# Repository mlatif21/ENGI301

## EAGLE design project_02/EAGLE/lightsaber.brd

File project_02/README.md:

# Lightsaber PCB Design

This directory in the repository contains the files for Project02, creating a circuit board based on our implemented project using PocketBeagle. All files necessary for PCB manufacturing are found here.

The docs folder contains the project 02 proposal with mechanical block diagram. It also contains a PDF of the schematics and images of the top and bottom layers of the board.

The EAGLE folder contains the library (lbr), schematics (sch), and layout (brd) files for the PCB design.
The MFG sub-folder contains the manufacturing files (Gerber, Drill, and Assembly) generated from default CAM settings.

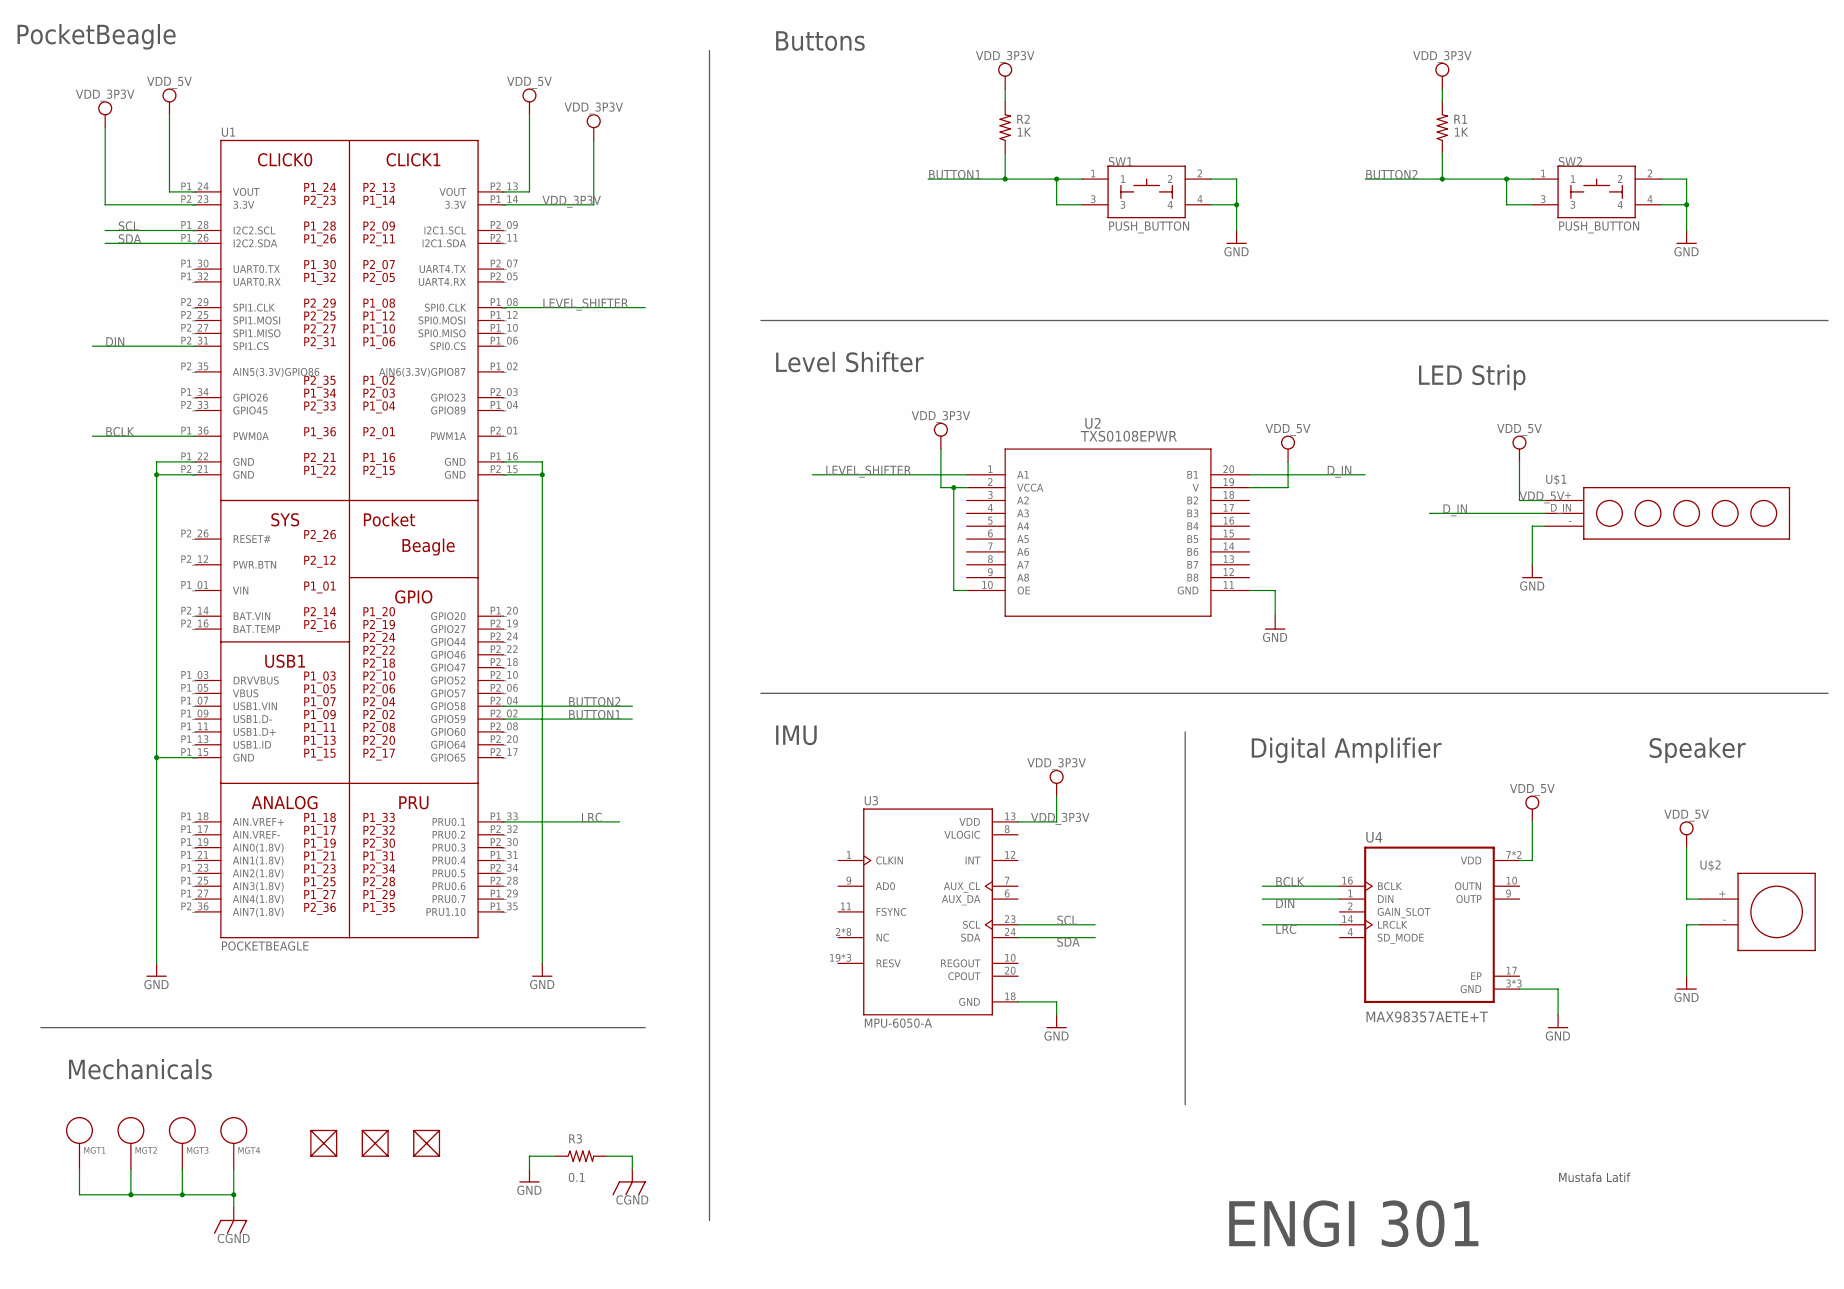
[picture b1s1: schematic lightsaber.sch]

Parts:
FUD1, FUD2, FUD3: FIDUCIAL; FIDUCIAL_40MIL
MGT1, MGT2, MGT3, MGT4: MOUNTING_HOLE
R1, R2: 1K; R0603
R3: 0.1; R0805
SW1, SW2: PUSH_BUTTON; BUTTON_12.5MM
U1: POCKETBEAGLE
U2: TXS0108EPWR; PW20
U3: MPU-6050-A; QFN50P400X400X95-24N
U4: MAX98357AETE+T; QFN50P300X300X80-17N
U$1: LED_LIGHT_STRIP
U$2: SPEAKER

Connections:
BAT.VIN: U1.P2_14 (BAT.VIN)
BCLK: U1.P1_36 (PWM0A), U4.16 (BCLK)
BUTTON1: R2.1, SW1.1, SW1.3, U1.P2_02 (GPIO59)
BUTTON2: R1.1, SW2.1, SW2.3, U1.P2_04 (GPIO58)
CGND: MGT1.P$1, MGT2.P$1, MGT3.P$1, MGT4.P$1, R3.2
DIN: U1.P2_31 (SPI1.CS), U4.1 (DIN)
D_IN: U2.20 (B1), U$1.D_IN
EP: U4.17 (EP)
GND: R3.1, SW1.2, SW1.4, SW2.2, SW2.4, U1.P1_15 (GND), U1.P1_16 (GND), U1.P1_22 (GND), U1.P2_15 (GND), U1.P2_21 (GND), U2.11 (GND), U3.18 (GND), U4.3 (GND), U4.11 (GND), U4.15 (GND), U$1.- (GND), U$2.-
LEVEL_SHIFTER: U1.P1_08 (SPI0.CLK), U2.1 (A1)
LRC: U1.P1_33 (PRU0.1), U4.14 (LRCLK)
SCL: U1.P1_28 (I2C2.SCL), U3.23 (SCL)
SDA: U1.P1_26 (I2C2.SDA), U3.24 (SDA)
VDD_3P3V: R1.2, R2.2, U1.P1_14 (3.3V), U1.P2_23 (3.3V), U2.2 (VCCA), U2.10 (OE), U3.13 (VDD)
VDD_5V: U1.P1_24 (VOUT), U1.P2_13 (VOUT), U2.19 (V), U4.7 (VDD), U4.8 (VDD), U$1.+ (+5V), U$2.+
VIN: U1.P1_01 (VIN)
VLOGIC: U3.8 (VLOGIC)

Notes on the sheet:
PocketBeagle
Buttons
Level Shifter
LED Strip
IMU
Digital Amplifier
Speaker
Mechanicals
ENGI 301
Mustafa Latif

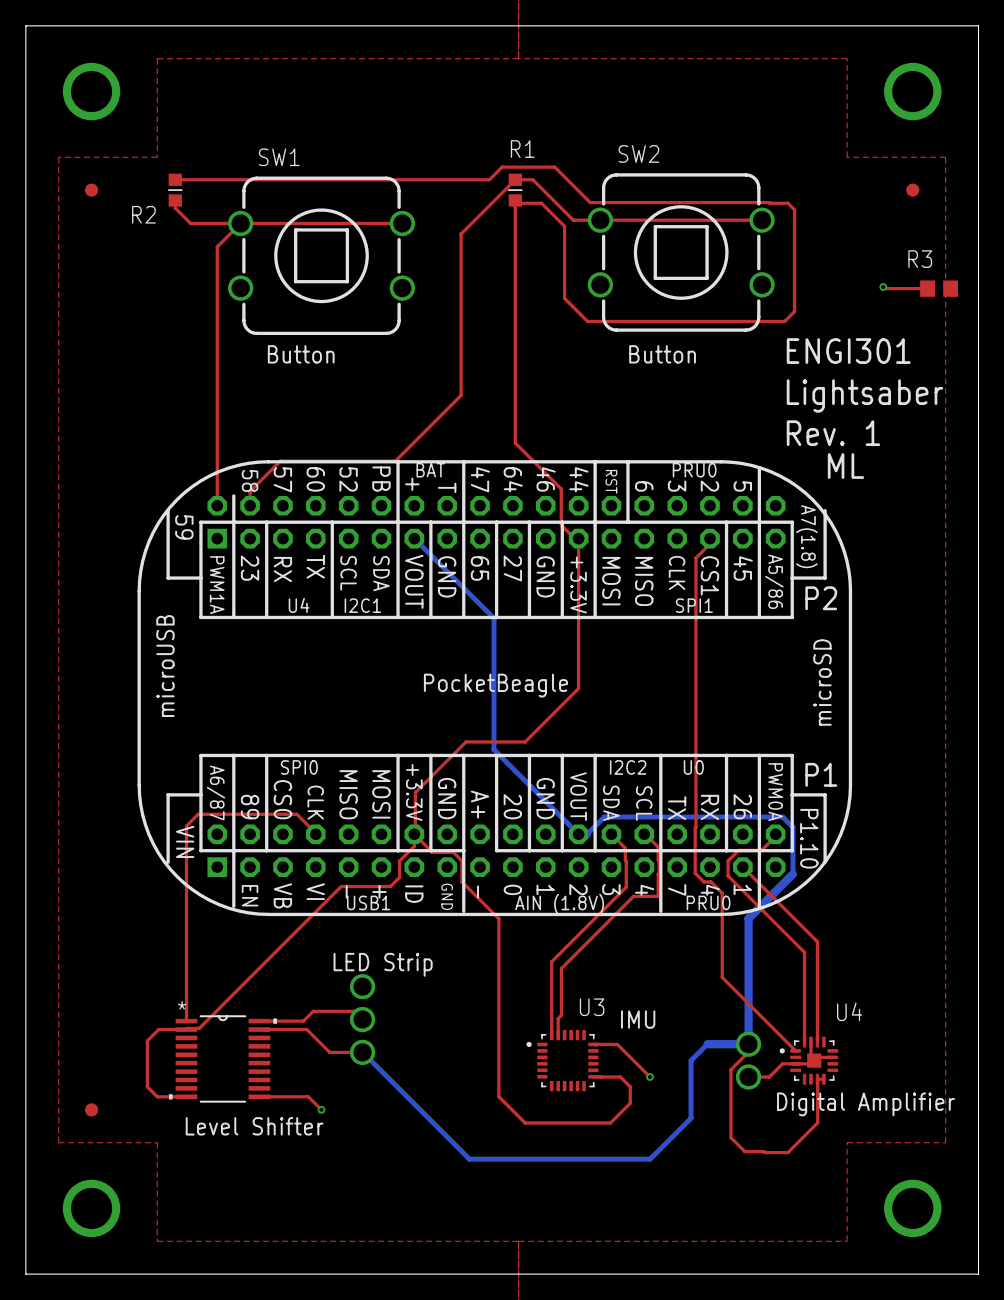
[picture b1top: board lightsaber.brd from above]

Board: 4 copper layers, 73.7 x 96.5 mm, 18 parts (0 on the bottom side), 13 nets.

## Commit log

2024-09-30 Create docs folder
2024-09-30 Create project presentation
2024-10-02 adding simple calculator
2024-10-06 small update
2024-10-08 added support for additional operations and python 2
2024-10-08 added blink_USR3.py program to blink USR3 LED at 5Hz
2024-10-09 adding button.py
2024-12-20 Create folder for project_02
2024-12-20 create EAGLE folder

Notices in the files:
parts and their libraries:
COPYRIGHT: Copyright (C) 2024 Ultra Librarian. All rights reserved.
